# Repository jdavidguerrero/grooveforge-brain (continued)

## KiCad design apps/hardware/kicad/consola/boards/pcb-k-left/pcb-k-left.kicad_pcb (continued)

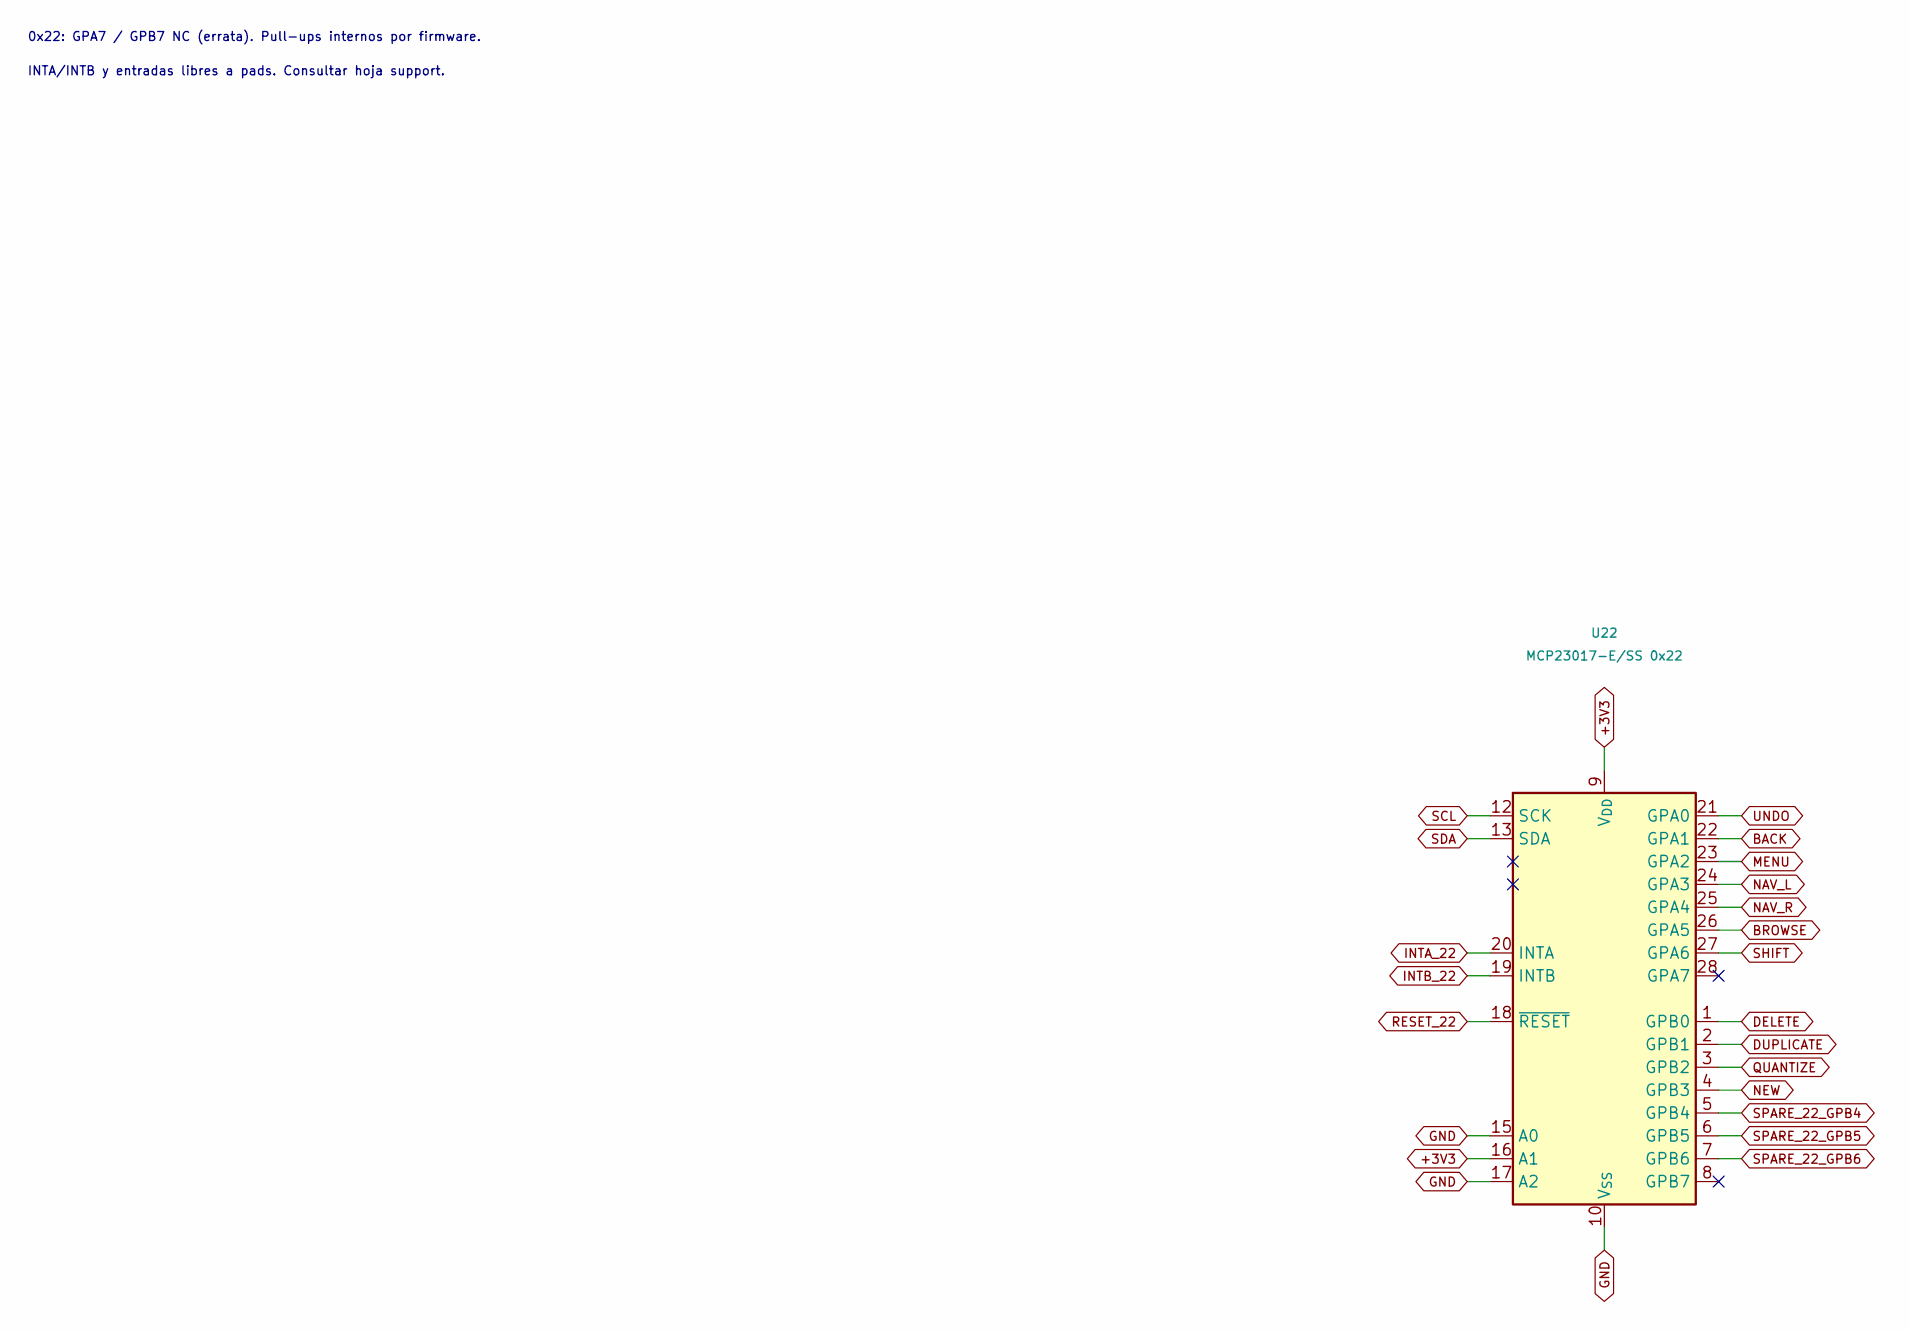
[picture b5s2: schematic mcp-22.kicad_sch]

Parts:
U22: MCP23017-E/SS 0x22; SSOP-28_5.3x10.2mm_P0.65mm; LCSC C506653

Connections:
+3V3: U22.9 (V_{DD}), U22.16 (A1); also elsewhere on the board
BACK: U22.22 (GPA1); also elsewhere on the board
BROWSE: U22.26 (GPA5); also elsewhere on the board
DELETE: U22.1 (GPB0); also elsewhere on the board
DUPLICATE: U22.2 (GPB1); also elsewhere on the board
GND: U22.10 (V_{SS}), U22.15 (A0), U22.17 (A2); also elsewhere on the board
INTA_22: U22.20 (INTA); also elsewhere on the board
INTB_22: U22.19 (INTB); also elsewhere on the board
MENU: U22.23 (GPA2); also elsewhere on the board
NAV_L: U22.24 (GPA3); also elsewhere on the board
NAV_R: U22.25 (GPA4); also elsewhere on the board
NEW: U22.4 (GPB3); also elsewhere on the board
QUANTIZE: U22.3 (GPB2); also elsewhere on the board
RESET_22: U22.18 (~RESET); also elsewhere on the board
SCL: U22.12 (SCK); also elsewhere on the board
SDA: U22.13 (SDA); also elsewhere on the board
SHIFT: U22.27 (GPA6); also elsewhere on the board
SPARE_22_GPB4: U22.5 (GPB4); also elsewhere on the board
SPARE_22_GPB5: U22.6 (GPB5); also elsewhere on the board
SPARE_22_GPB6: U22.7 (GPB6); also elsewhere on the board
UNDO: U22.21 (GPA0); also elsewhere on the board

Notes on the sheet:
0x22: GPA7 / GPB7 NC (errata). Pull-ups internos por firmware.
INTA/INTB y entradas libres a pads. Consultar hoja support.

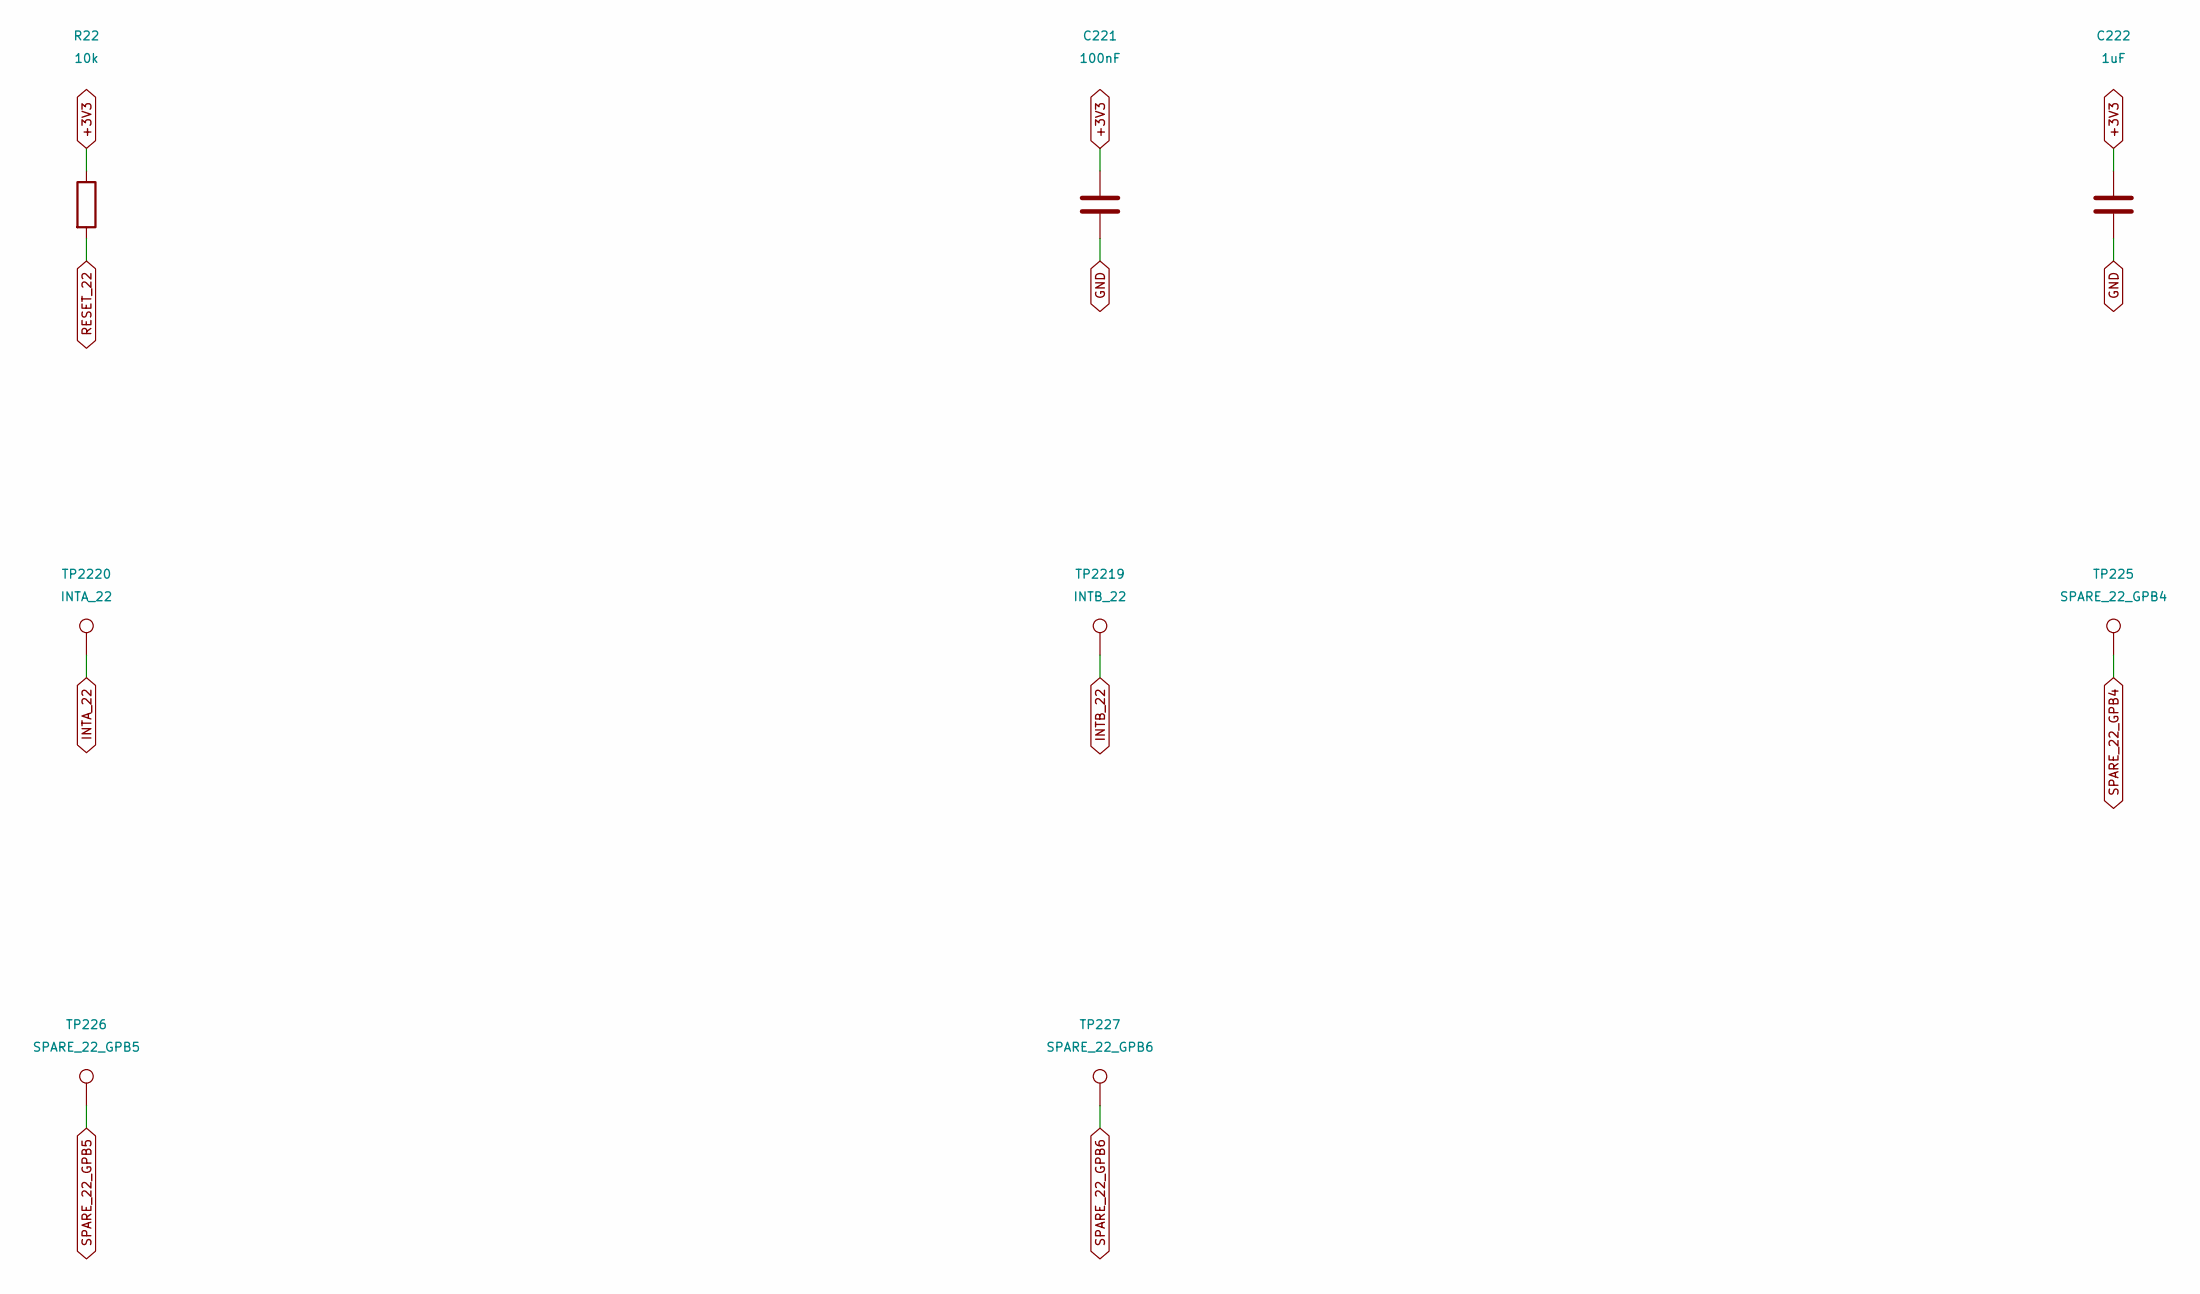
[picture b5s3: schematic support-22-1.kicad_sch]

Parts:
C221: 100nF; C_0805_2012Metric; MPN CC0805KRX7R9BB104; LCSC C49678
C222: 1uF; C_0805_2012Metric; MPN FCC0805B105K500FT; LCSC C5137478
R22: 10k; R_0805_2012Metric; MPN 0805W8F1002T5E; LCSC C17414
TP225: SPARE_22_GPB4; TestPoint_Pad_D1.5mm
TP226: SPARE_22_GPB5; TestPoint_Pad_D1.5mm
TP227: SPARE_22_GPB6; TestPoint_Pad_D1.5mm
TP2219: INTB_22; TestPoint_Pad_D1.5mm
TP2220: INTA_22; TestPoint_Pad_D1.5mm

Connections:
+3V3: C221.1, C222.1, R22.1; also elsewhere on the board
GND: C221.2, C222.2; also elsewhere on the board
INTA_22: TP2220.1; also elsewhere on the board
INTB_22: TP2219.1; also elsewhere on the board
RESET_22: R22.2; also elsewhere on the board
SPARE_22_GPB4: TP225.1; also elsewhere on the board
SPARE_22_GPB5: TP226.1; also elsewhere on the board
SPARE_22_GPB6: TP227.1; also elsewhere on the board

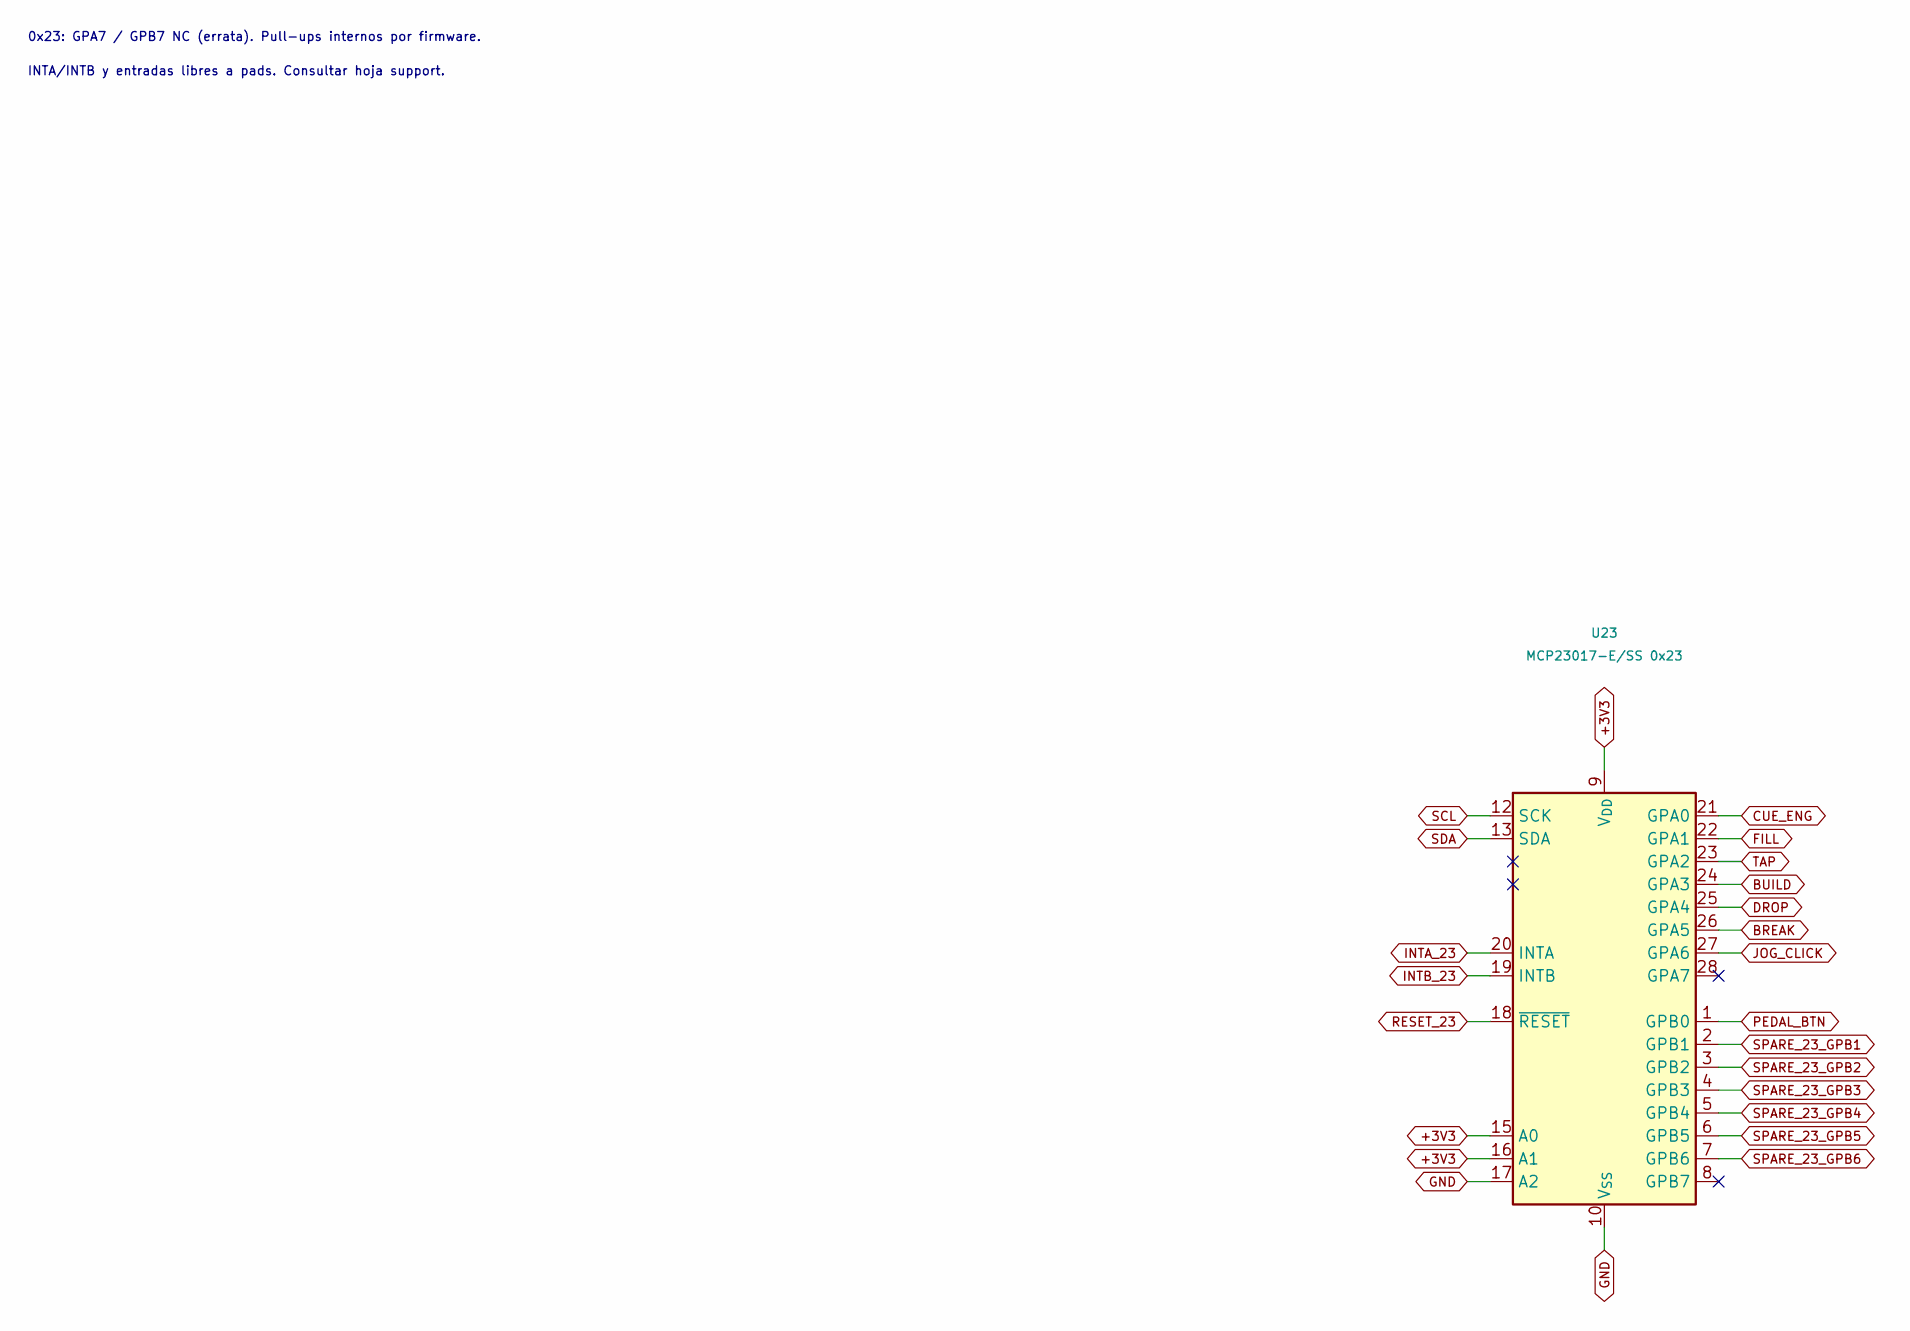
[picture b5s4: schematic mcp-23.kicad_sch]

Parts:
U23: MCP23017-E/SS 0x23; SSOP-28_5.3x10.2mm_P0.65mm; MPN MCP23017-E/SS; LCSC C506653

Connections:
+3V3: U23.9 (V_{DD}), U23.15 (A0), U23.16 (A1); also elsewhere on the board
BREAK: U23.26 (GPA5); also elsewhere on the board
BUILD: U23.24 (GPA3); also elsewhere on the board
CUE_ENG: U23.21 (GPA0); also elsewhere on the board
DROP: U23.25 (GPA4); also elsewhere on the board
FILL: U23.22 (GPA1); also elsewhere on the board
GND: U23.10 (V_{SS}), U23.17 (A2); also elsewhere on the board
INTA_23: U23.20 (INTA); also elsewhere on the board
INTB_23: U23.19 (INTB); also elsewhere on the board
JOG_CLICK: U23.27 (GPA6); also elsewhere on the board
PEDAL_BTN: U23.1 (GPB0); also elsewhere on the board
RESET_23: U23.18 (~RESET); also elsewhere on the board
SCL: U23.12 (SCK); also elsewhere on the board
SDA: U23.13 (SDA); also elsewhere on the board
SPARE_23_GPB1: U23.2 (GPB1); also elsewhere on the board
SPARE_23_GPB2: U23.3 (GPB2); also elsewhere on the board
SPARE_23_GPB3: U23.4 (GPB3); also elsewhere on the board
SPARE_23_GPB4: U23.5 (GPB4); also elsewhere on the board
SPARE_23_GPB5: U23.6 (GPB5); also elsewhere on the board
SPARE_23_GPB6: U23.7 (GPB6); also elsewhere on the board
TAP: U23.23 (GPA2); also elsewhere on the board

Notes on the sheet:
0x23: GPA7 / GPB7 NC (errata). Pull-ups internos por firmware.
INTA/INTB y entradas libres a pads. Consultar hoja support.

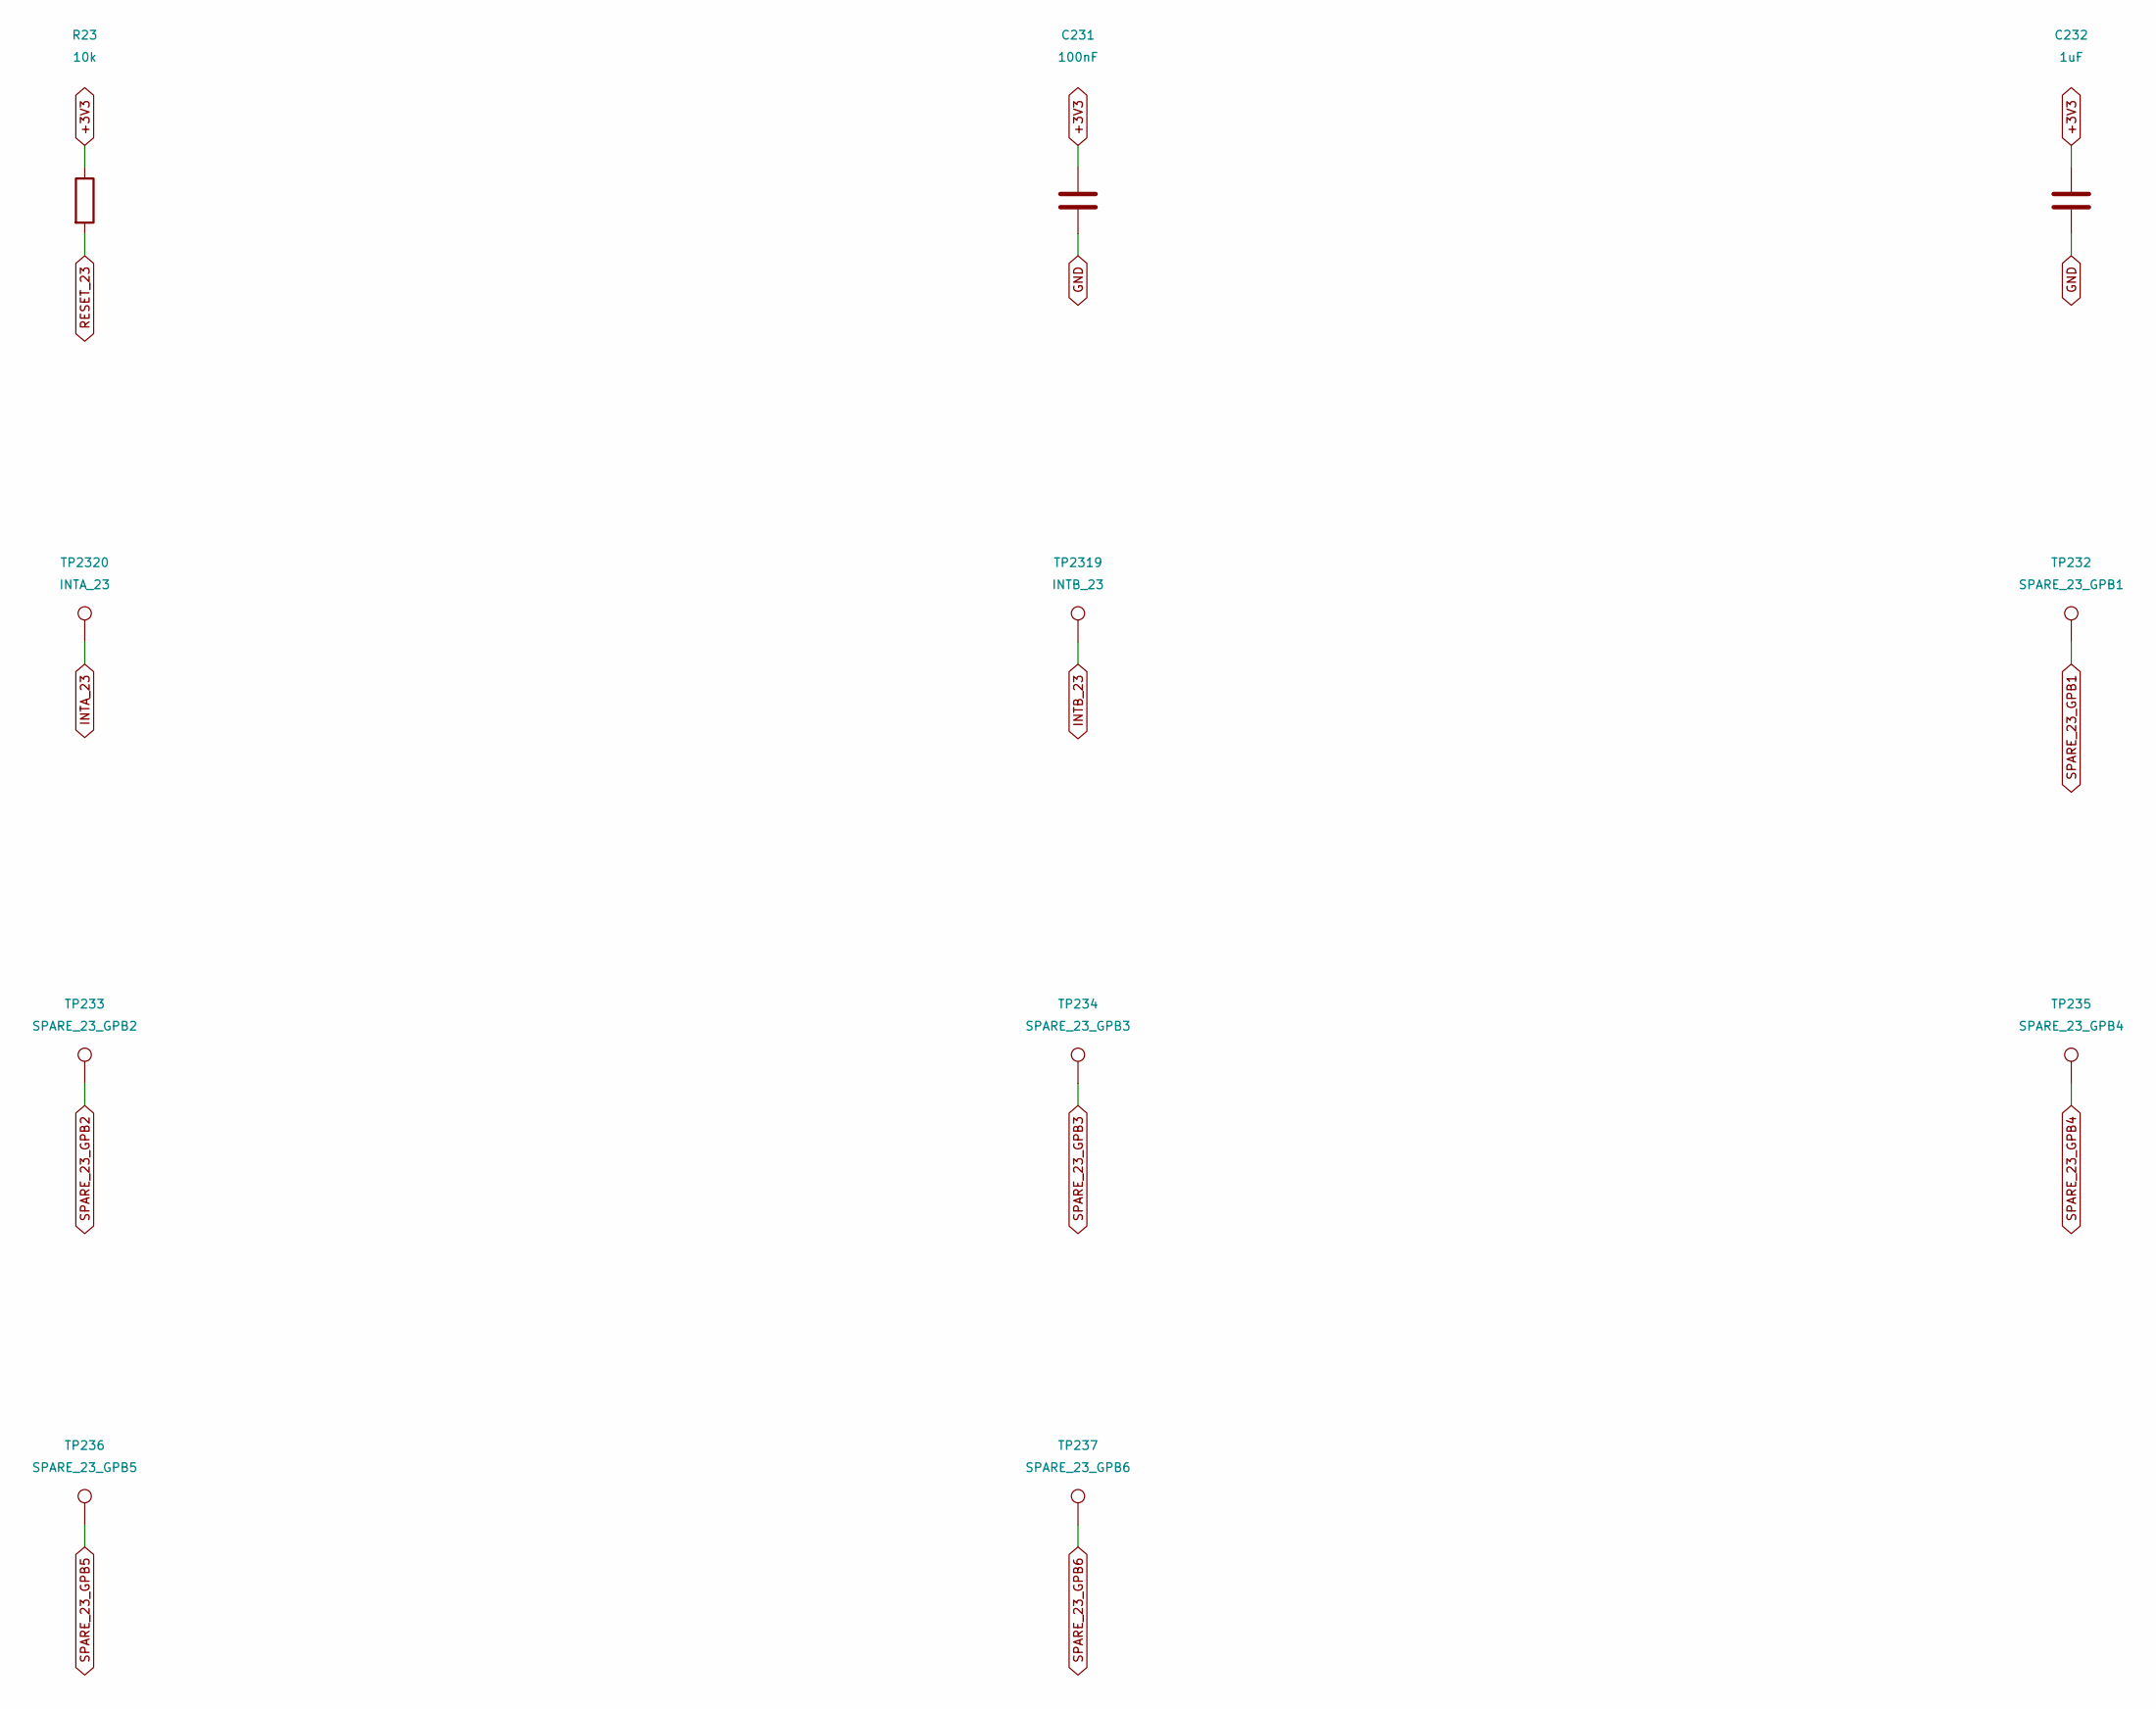
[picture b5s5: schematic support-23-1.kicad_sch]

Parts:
C231: 100nF; C_0805_2012Metric; LCSC C49678
C232: 1uF; C_0805_2012Metric; LCSC C5137478
R23: 10k; R_0805_2012Metric; LCSC C17414
TP232: SPARE_23_GPB1; TestPoint_Pad_D1.5mm
TP233: SPARE_23_GPB2; TestPoint_Pad_D1.5mm
TP234: SPARE_23_GPB3; TestPoint_Pad_D1.5mm
TP235: SPARE_23_GPB4; TestPoint_Pad_D1.5mm
TP236: SPARE_23_GPB5; TestPoint_Pad_D1.5mm
TP237: SPARE_23_GPB6; TestPoint_Pad_D1.5mm
TP2319: INTB_23; TestPoint_Pad_D1.5mm
TP2320: INTA_23; TestPoint_Pad_D1.5mm

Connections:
+3V3: C231.1, C232.1, R23.1; also elsewhere on the board
GND: C231.2, C232.2; also elsewhere on the board
INTA_23: TP2320.1; also elsewhere on the board
INTB_23: TP2319.1; also elsewhere on the board
RESET_23: R23.2; also elsewhere on the board
SPARE_23_GPB1: TP232.1; also elsewhere on the board
SPARE_23_GPB2: TP233.1; also elsewhere on the board
SPARE_23_GPB3: TP234.1; also elsewhere on the board
SPARE_23_GPB4: TP235.1; also elsewhere on the board
SPARE_23_GPB5: TP236.1; also elsewhere on the board
SPARE_23_GPB6: TP237.1; also elsewhere on the board

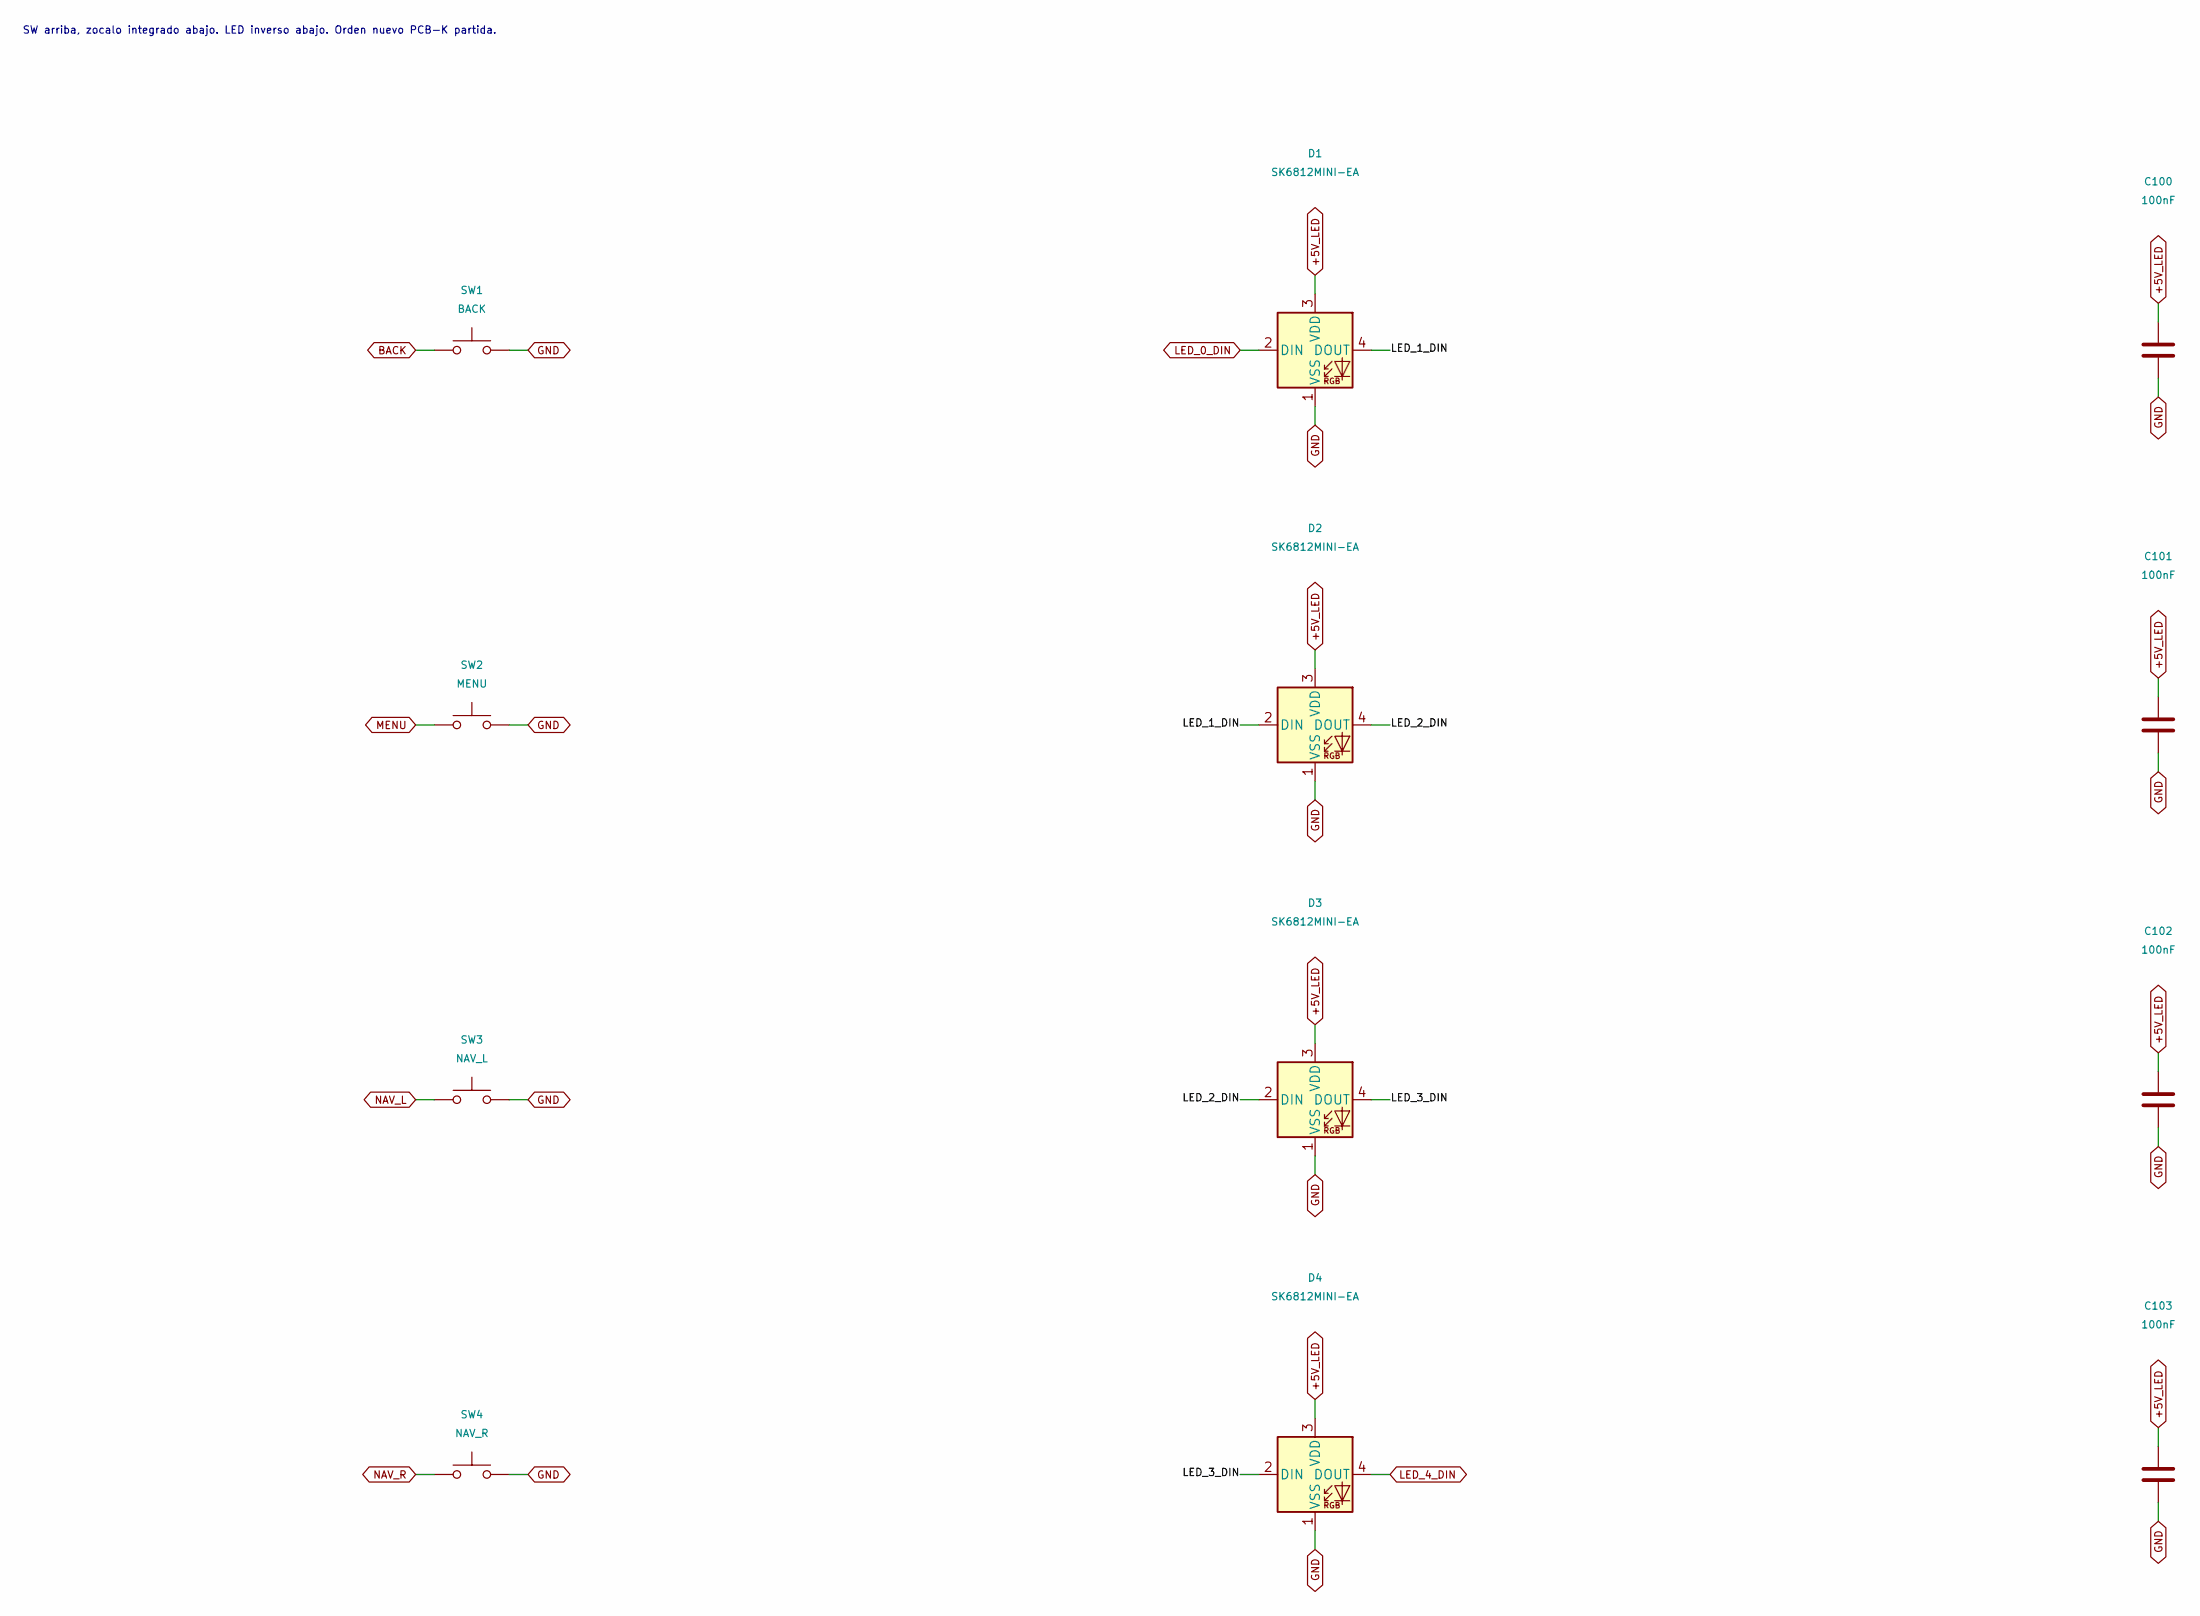
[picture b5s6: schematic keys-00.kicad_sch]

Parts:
C100, C101, C102, C103: 100nF; C_0805_2012Metric; MPN CC0805KRX7R9BB104; LCSC C49678
D1, D2, D3, D4: SK6812MINI-EA; SK6812MINI-EA_ReverseMount; MPN SK6812MINI-EA; LCSC C5378731
SW1: BACK; Kailh_Choc_V2_PG1353_Hotswap
SW2: MENU; Kailh_Choc_V2_PG1353_Hotswap
SW3: NAV_L; Kailh_Choc_V2_PG1353_Hotswap
SW4: NAV_R; Kailh_Choc_V2_PG1353_Hotswap

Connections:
+5V_LED: C100.1, C101.1, C102.1, C103.1, D1.3 (VDD), D2.3 (VDD), D3.3 (VDD), D4.3 (VDD); also elsewhere on the board
/keys-00/LED_1_DIN: D1.4 (DOUT), D2.2 (DIN)
/keys-00/LED_2_DIN: D2.4 (DOUT), D3.2 (DIN)
/keys-00/LED_3_DIN: D3.4 (DOUT), D4.2 (DIN)
BACK: SW1.1; also elsewhere on the board
GND: C100.2, C101.2, C102.2, C103.2, D1.1 (VSS), D2.1 (VSS), D3.1 (VSS), D4.1 (VSS), SW1.2, SW2.2, SW3.2, SW4.2; also elsewhere on the board
LED_0_DIN: D1.2 (DIN); also elsewhere on the board
LED_4_DIN: D4.4 (DOUT); also elsewhere on the board
MENU: SW2.1; also elsewhere on the board
NAV_L: SW3.1; also elsewhere on the board
NAV_R: SW4.1; also elsewhere on the board

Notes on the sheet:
SW arriba, zocalo integrado abajo. LED inverso abajo. Orden nuevo PCB-K partida.

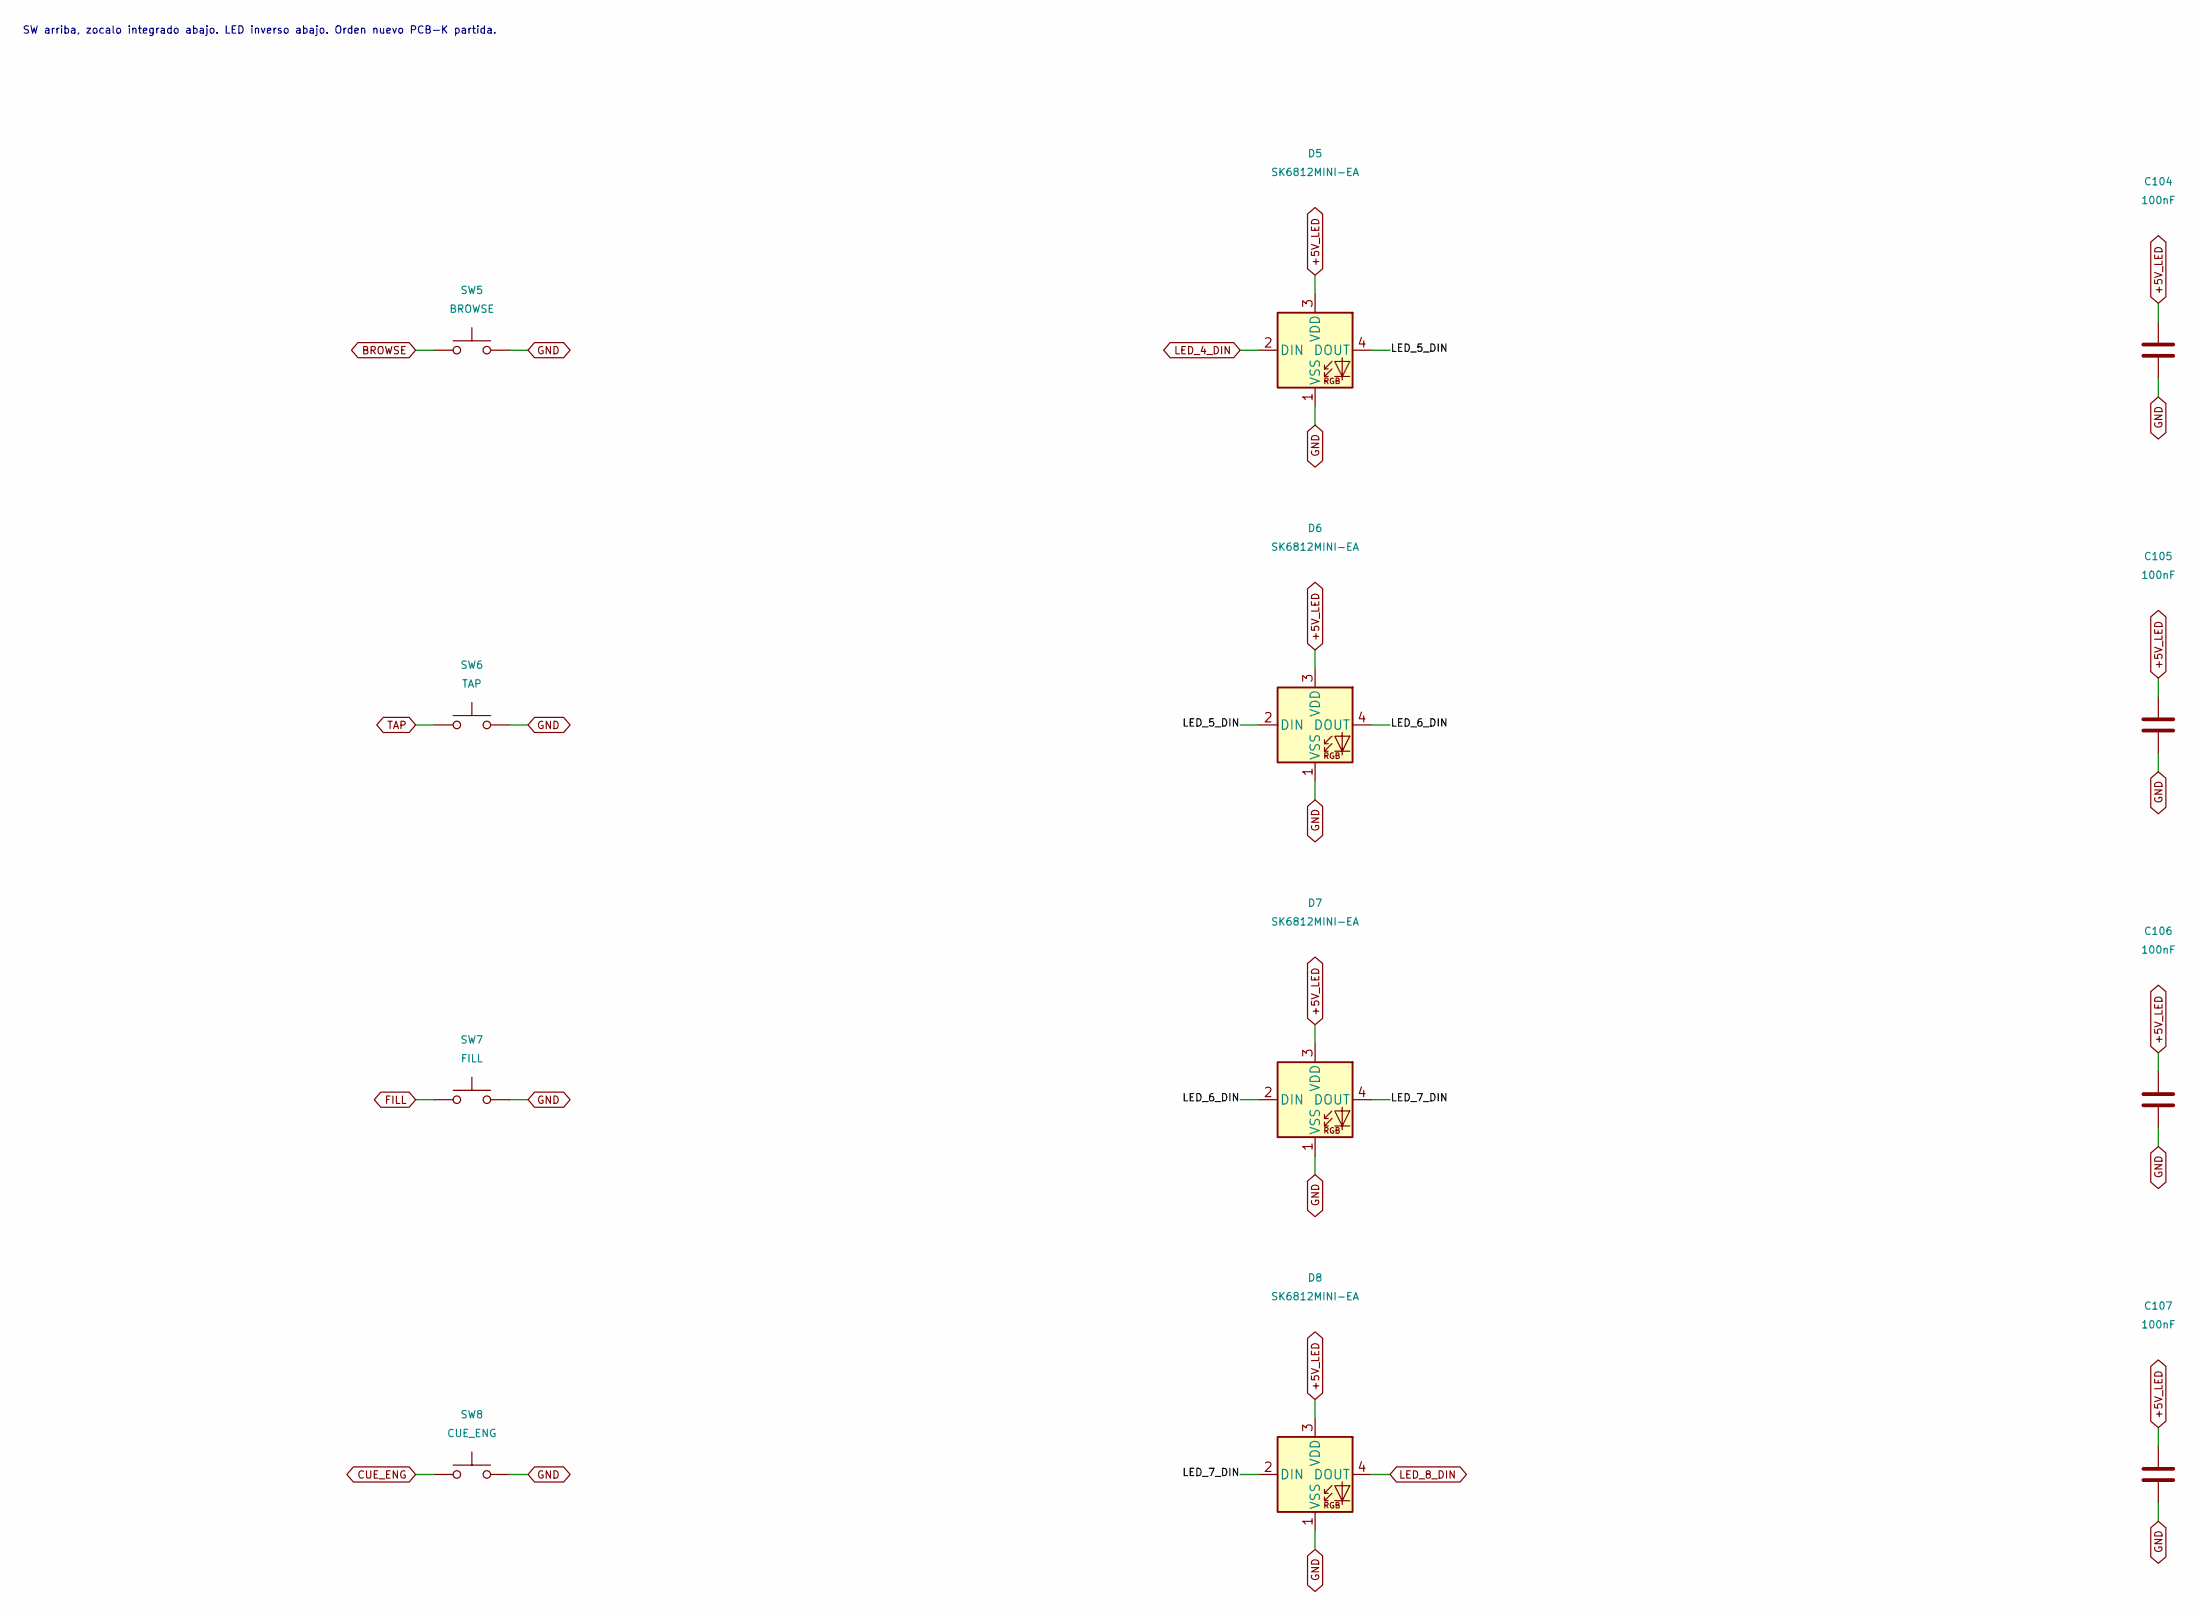
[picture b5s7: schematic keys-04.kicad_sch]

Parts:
C104, C105, C106, C107: 100nF; C_0805_2012Metric; MPN CC0805KRX7R9BB104; LCSC C49678
D5, D6, D7, D8: SK6812MINI-EA; SK6812MINI-EA_ReverseMount; MPN SK6812MINI-EA; LCSC C5378731
SW5: BROWSE; Kailh_Choc_V2_PG1353_Hotswap
SW6: TAP; Kailh_Choc_V2_PG1353_Hotswap
SW7: FILL; Kailh_Choc_V2_PG1353_Hotswap
SW8: CUE_ENG; Kailh_Choc_V2_PG1353_Hotswap

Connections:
+5V_LED: C104.1, C105.1, C106.1, C107.1, D5.3 (VDD), D6.3 (VDD), D7.3 (VDD), D8.3 (VDD); also elsewhere on the board
/keys-04/LED_5_DIN: D5.4 (DOUT), D6.2 (DIN)
/keys-04/LED_6_DIN: D6.4 (DOUT), D7.2 (DIN)
/keys-04/LED_7_DIN: D7.4 (DOUT), D8.2 (DIN)
BROWSE: SW5.1; also elsewhere on the board
CUE_ENG: SW8.1; also elsewhere on the board
FILL: SW7.1; also elsewhere on the board
GND: C104.2, C105.2, C106.2, C107.2, D5.1 (VSS), D6.1 (VSS), D7.1 (VSS), D8.1 (VSS), SW5.2, SW6.2, SW7.2, SW8.2; also elsewhere on the board
LED_4_DIN: D5.2 (DIN); also elsewhere on the board
LED_8_DIN: D8.4 (DOUT); also elsewhere on the board
TAP: SW6.1; also elsewhere on the board

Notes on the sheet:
SW arriba, zocalo integrado abajo. LED inverso abajo. Orden nuevo PCB-K partida.
